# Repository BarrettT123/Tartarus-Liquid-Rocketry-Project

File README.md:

Files and photos related to my work on the Tartarus Project of the Space Hardware Club

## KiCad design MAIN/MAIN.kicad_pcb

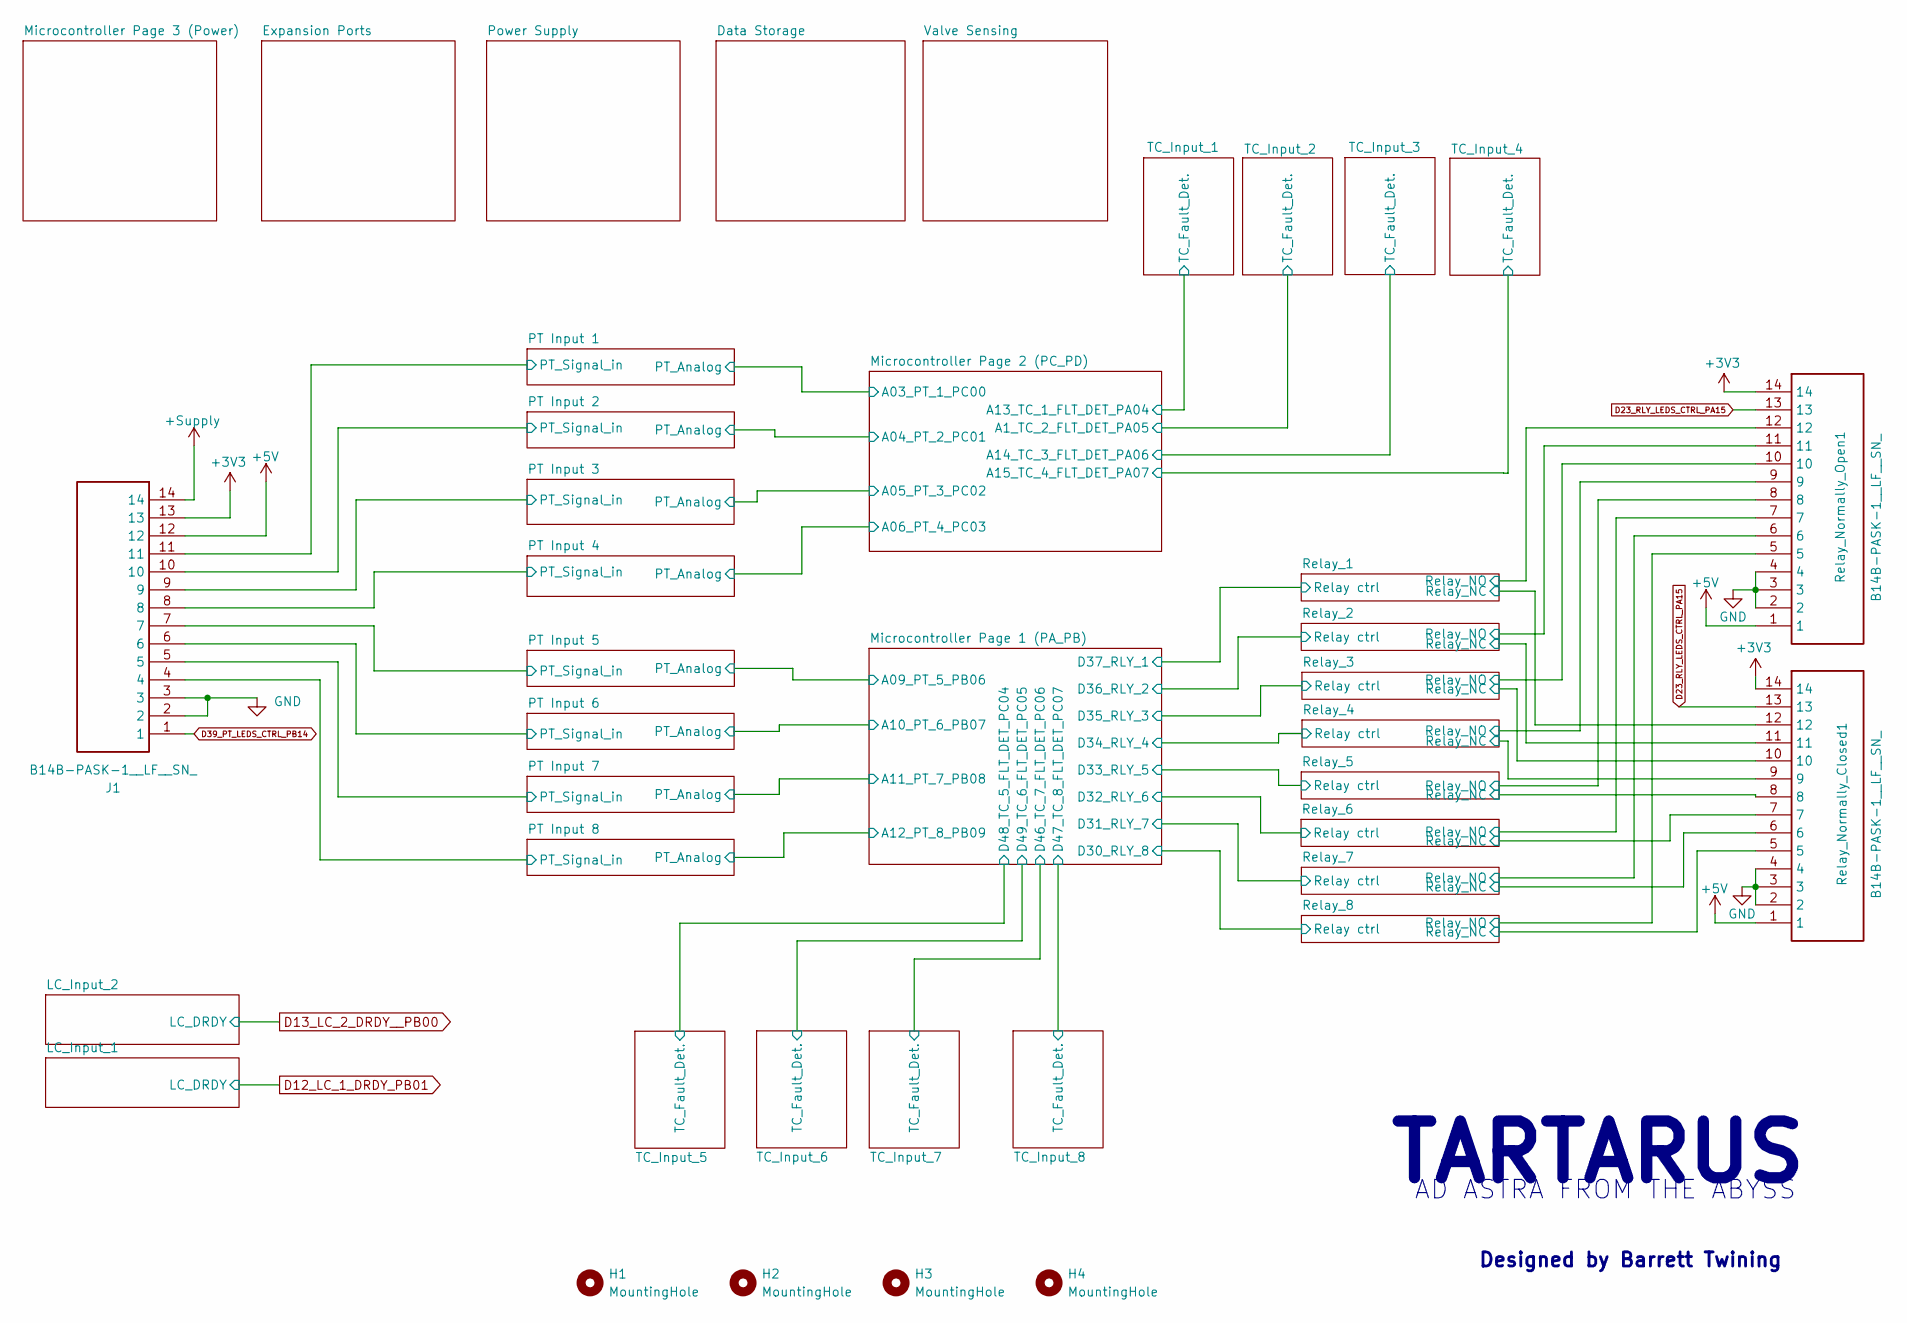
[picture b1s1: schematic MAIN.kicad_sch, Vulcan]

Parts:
H1, H2, H3, H4: MountingHole; MountingHole_3.2mm_M3_ISO7380_Pad_TopBottom
J1: B14B-PASK-1__LF__SN_; B14BPASK1LFSN; Manufacturer_Part_Number B14B-PASK-1 (LF)(SN)
Relay_Normally_Closed1: B14B-PASK-1__LF__SN_; B14BPASK1LFSN; Manufacturer_Part_Number B14B-PASK-1 (LF)(SN)
Relay_Normally_Open1: B14B-PASK-1__LF__SN_; B14BPASK1LFSN; Manufacturer_Part_Number B14B-PASK-1 (LF)(SN)

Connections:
+3V3: J1.13, Relay_Normally_Closed1.14, Relay_Normally_Open1.14; also elsewhere on the board
+5V: J1.12, Relay_Normally_Closed1.1, Relay_Normally_Open1.1; also elsewhere on the board
+Supply: J1.14; also elsewhere on the board
/PT Input 1/PT_Signal_in: J1.11; also elsewhere on the board
/PT Input 2/PT_Signal_in: J1.10; also elsewhere on the board
/PT Input 3/PT_Signal_in: J1.9; also elsewhere on the board
/PT Input 4/PT_Signal_in: J1.8; also elsewhere on the board
/PT Input 5/PT_Signal_in: J1.7; also elsewhere on the board
/PT Input 6/PT_Signal_in: J1.6; also elsewhere on the board
/PT Input 7/PT_Signal_in: J1.5; also elsewhere on the board
/PT Input 8/PT_Signal_in: J1.4; also elsewhere on the board
/Relay_1/Relay_NC: Relay_Normally_Closed1.12; also elsewhere on the board
/Relay_1/Relay_NO: Relay_Normally_Open1.12; also elsewhere on the board
/Relay_2/Relay_NC: Relay_Normally_Closed1.11; also elsewhere on the board
/Relay_2/Relay_NO: Relay_Normally_Open1.11; also elsewhere on the board
/Relay_3/Relay_NC: Relay_Normally_Closed1.10; also elsewhere on the board
/Relay_3/Relay_NO: Relay_Normally_Open1.10; also elsewhere on the board
/Relay_4/Relay_NC: Relay_Normally_Closed1.9; also elsewhere on the board
/Relay_4/Relay_NO: Relay_Normally_Open1.9; also elsewhere on the board
/Relay_5/Relay_NC: Relay_Normally_Closed1.8; also elsewhere on the board
/Relay_5/Relay_NO: Relay_Normally_Open1.8; also elsewhere on the board
/Relay_6/Relay_NC: Relay_Normally_Closed1.7; also elsewhere on the board
/Relay_6/Relay_NO: Relay_Normally_Open1.7; also elsewhere on the board
/Relay_7/Relay_NC: Relay_Normally_Closed1.6; also elsewhere on the board
/Relay_7/Relay_NO: Relay_Normally_Open1.6; also elsewhere on the board
/Relay_8/Relay_NC: Relay_Normally_Closed1.5; also elsewhere on the board
/Relay_8/Relay_NO: Relay_Normally_Open1.5; also elsewhere on the board
D23_RLY_LEDS_CTRL_PA15: Relay_Normally_Closed1.13, Relay_Normally_Open1.13; also elsewhere on the board
D39_PT_LEDS_CTRL_PB14: J1.1; also elsewhere on the board
GND: J1.2, J1.3, Relay_Normally_Closed1.2, Relay_Normally_Closed1.3, Relay_Normally_Closed1.4, Relay_Normally_Open1.2, Relay_Normally_Open1.3, Relay_Normally_Open1.4; also elsewhere on the board

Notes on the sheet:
Designed by Barrett Twining
TARTARUS
AD ASTRA FROM THE ABYSS

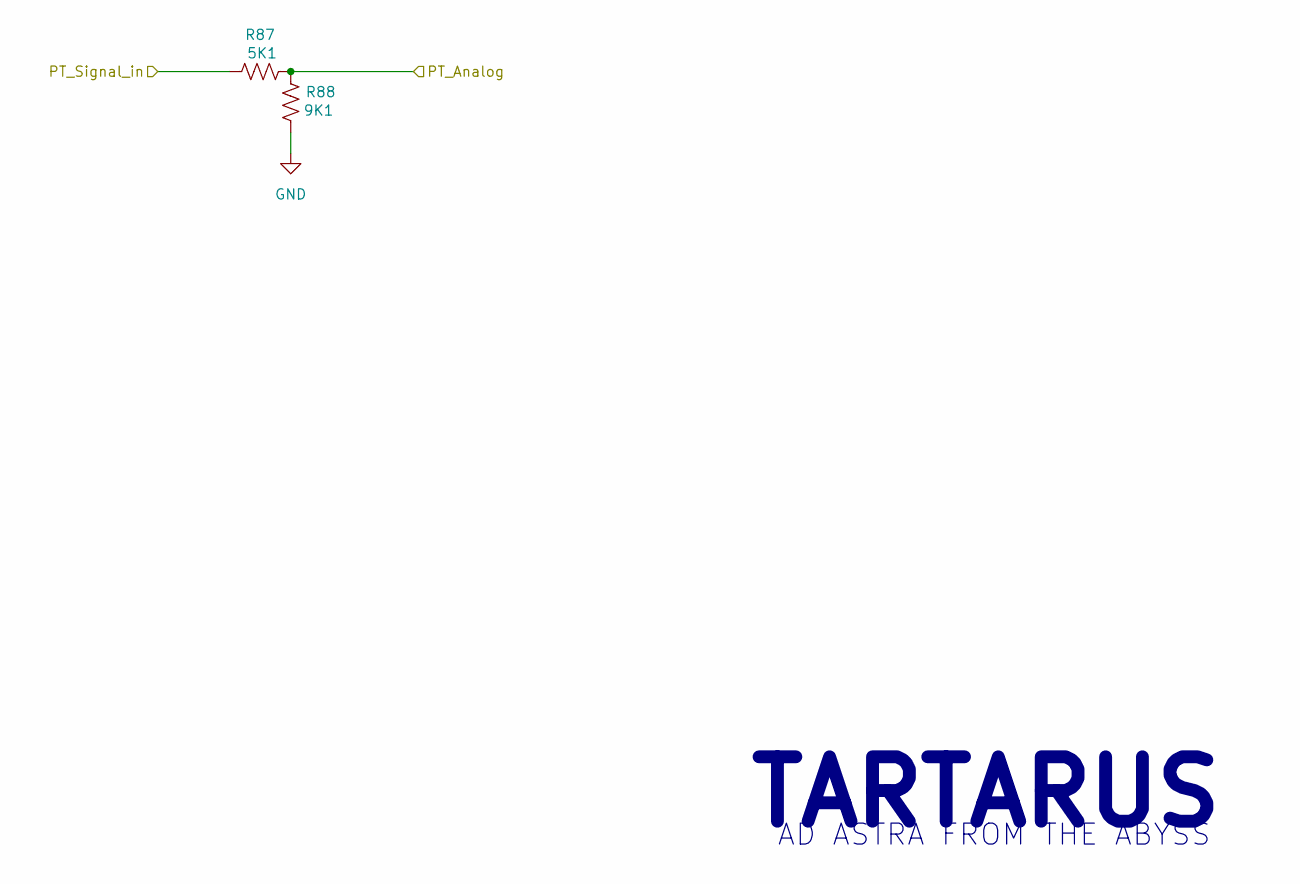
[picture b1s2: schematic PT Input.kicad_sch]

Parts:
R87: 5K1; R_0603_1608Metric
R88: 9K1; R_0603_1608Metric

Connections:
/PT Input 1/PT_Signal_in: R87.1; also elsewhere on the board
A03_PT_1_PC00: R87.2, R88.1; also elsewhere on the board
GND: R88.2; also elsewhere on the board

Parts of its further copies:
R89, R91, R93, R95, R97, R99, R101: 5K1; R_0603_1608Metric
R90, R92, R94, R96, R98, R100, R102: 9K1; R_0603_1608Metric

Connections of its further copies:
/Microcontroller Page 1 (PA_PB)/A09_PT_5_PB06: R95.2, R96.1; also elsewhere on the board
/Microcontroller Page 1 (PA_PB)/A10_PT_6_PB07: R97.2, R98.1; also elsewhere on the board
/Microcontroller Page 1 (PA_PB)/A11_PT_7_PB08: R99.2, R100.1; also elsewhere on the board
/Microcontroller Page 1 (PA_PB)/A12_PT_8_PB09: R101.2, R102.1; also elsewhere on the board
/PT Input 2/PT_Signal_in: R89.1; also elsewhere on the board
/PT Input 3/PT_Signal_in: R91.1; also elsewhere on the board
/PT Input 4/PT_Signal_in: R93.1; also elsewhere on the board
/PT Input 5/PT_Signal_in: R95.1; also elsewhere on the board
/PT Input 6/PT_Signal_in: R97.1; also elsewhere on the board
/PT Input 7/PT_Signal_in: R99.1; also elsewhere on the board
/PT Input 8/PT_Signal_in: R101.1; also elsewhere on the board
A04_PT_2_PC01: R89.2, R90.1; also elsewhere on the board
A05_PT_3_PC02: R91.2, R92.1; also elsewhere on the board
A06_PT_4_PC03: R93.2, R94.1; also elsewhere on the board
GND: R90.2, R92.2, R94.2, R96.2, R98.2, R100.2, R102.2; also elsewhere on the board

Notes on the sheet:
AD ASTRA FROM THE ABYSS
TARTARUS

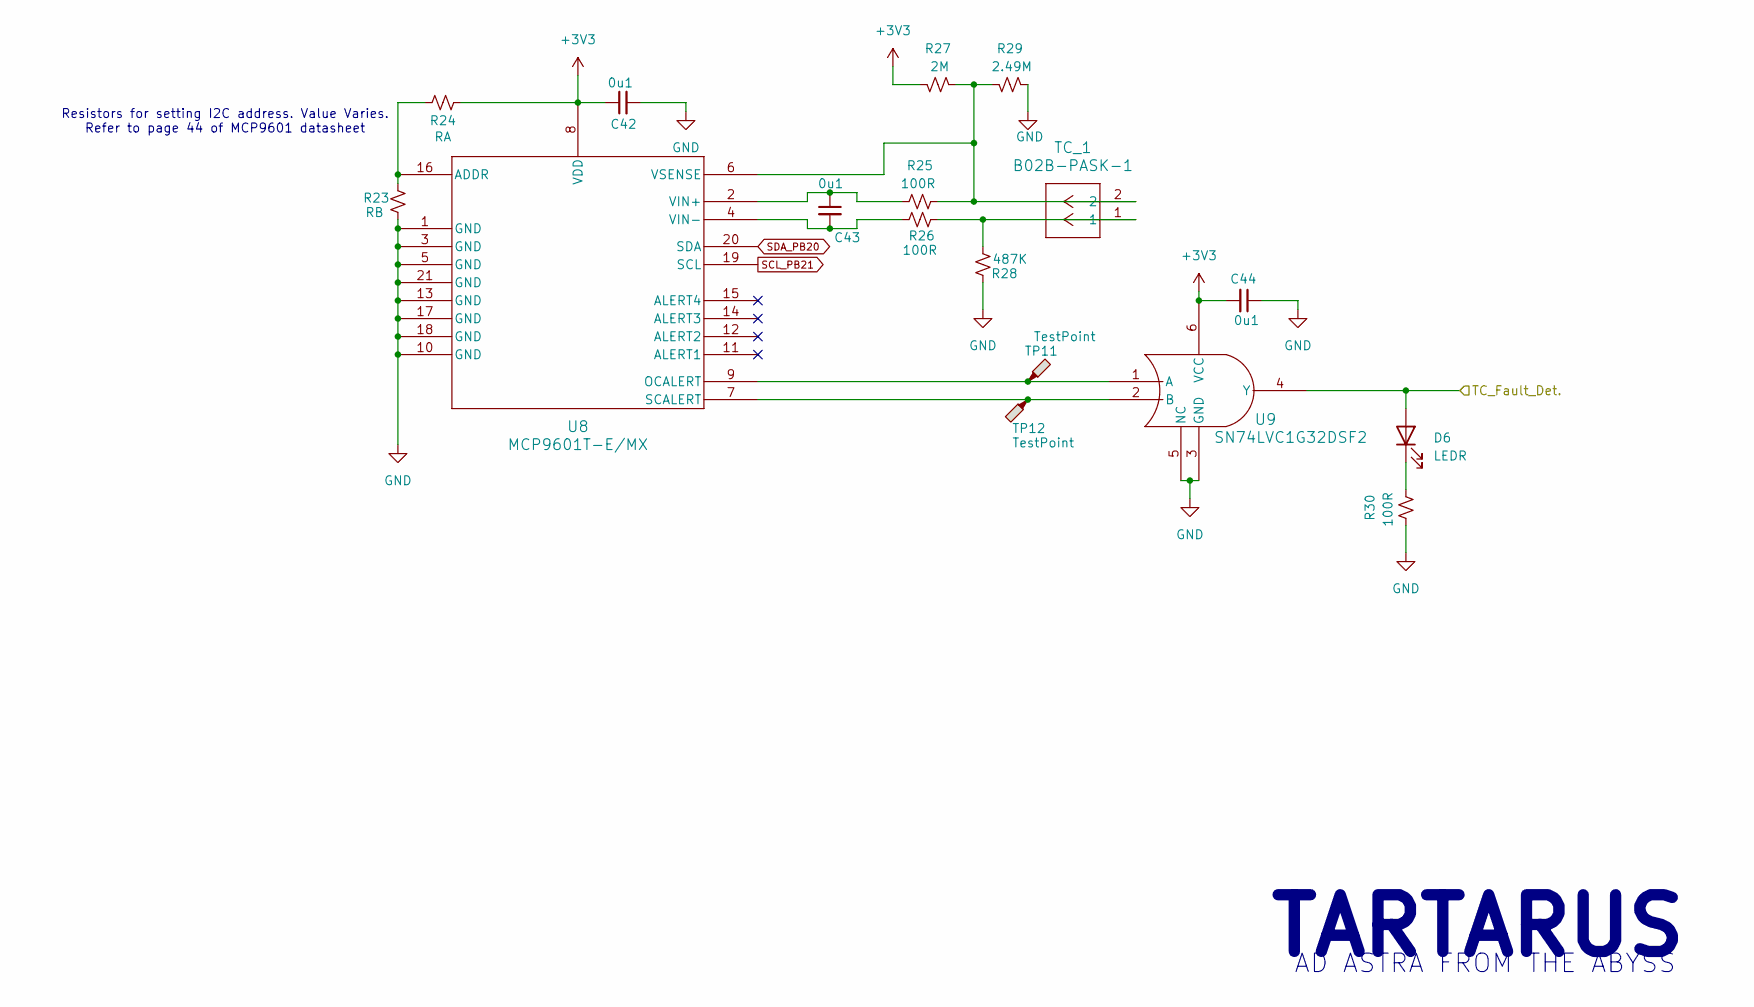
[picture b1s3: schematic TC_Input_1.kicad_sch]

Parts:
C42, C43, C44: 0u1; C_0603_1608Metric
D6: LEDR; LED_0603_1608Metric
R23: RB; R_0603_1608Metric
R24: RA; R_0603_1608Metric
R25, R26, R30: 100R; R_0603_1608Metric
R27: 2M; R_0603_1608Metric
R28: 487K; R_0603_1608Metric
R29: 2.49M; R_0603_1608Metric
TC_1: B02B-PASK-1; CONN_B02B-PASK-1_JST
TP11, TP12: TestPoint; TestPoint_Pad_D1.0mm
U8: MCP9601T-E/MX; MCP9601T_E_MX
U9: SN74LVC1G32DSF2; DSF6

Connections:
+3V3: C42.1, C44.2, R24.2, R27.2, U8.8 (VDD), U9.6 (VCC); also elsewhere on the board
/Microcontroller Page 2 (PC_PD)/A13_TC_1_FLT_DET_PA04: D6.2 (A), U9.4 (Y); also elsewhere on the board
GND: C42.2, C44.1, R23.1, R28.1, R29.1, R30.1, U8.1 (GND), U8.3 (GND), U8.5 (GND), U8.10 (GND), U8.13 (GND), U8.17 (GND), U8.18 (GND), U8.21 (GND), U9.3 (GND), U9.5 (NC); also elsewhere on the board
unnamed: D6.1 (K), R30.2
unnamed: R26.2, R28.2, TC_1.1
unnamed: R23.2, R24.1, U8.16 (ADDR)
unnamed: TP11.1, U8.9 (OCALERT), U9.1 (A)
unnamed: TP12.1, U8.7 (SCALERT), U9.2 (B)
unnamed: C43.1, R25.1, U8.2 (VIN+)
unnamed: C43.2, R26.1, U8.4 (VIN-)
unnamed: R25.2, R27.1, R29.2, TC_1.2, U8.6 (VSENSE)
SCL_PB21: U8.19 (SCL); also elsewhere on the board
SDA_PB20: U8.20 (SDA); also elsewhere on the board

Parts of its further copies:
C45, C46, C47, C48, C49, C50, C51, C52, C53, C54, C55, C56, C57, C58, C59, C60, C61, C62, C63, C64, C65: 0u1; C_0603_1608Metric
D7, D8, D9, D10, D11, D12, D13: LEDR; LED_0603_1608Metric
R31, R39, R47, R55, R63, R71, R79: RB; R_0603_1608Metric
R32, R40, R48, R56, R64, R72, R80: RA; R_0603_1608Metric
R33, R34, R38, R41, R42, R46, R49, R50, R54, R57, R58, R62, R65, R66, R70, R73, R74, R78, R81, R82, R86: 100R; R_0603_1608Metric
R35, R43, R51, R59, R67, R75, R83: 2M; R_0603_1608Metric
R36, R44, R52, R60, R68, R76, R84: 487K; R_0603_1608Metric
R37, R45, R53, R61, R69, R77, R85: 2.49M; R_0603_1608Metric
TC_2, TC_3, TC_4, TC_5, TC_6, TC_7, TC_8: B02B-PASK-1; CONN_B02B-PASK-1_JST
TP13, TP14, TP15, TP16, TP17, TP18, TP19, TP20, TP21, TP22, TP23, TP24, TP25, TP26: TestPoint; TestPoint_Pad_D1.0mm
U10, U12, U14, U16, U18, U20, U22: MCP9601T-E/MX; MCP9601T_E_MX
U11, U13, U15, U17, U19, U21, U23: SN74LVC1G32DSF2; DSF6

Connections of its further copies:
+3V3: C45.1, C47.2, C48.1, C50.2, C51.1, C53.2, C54.1, C56.2, C57.1, C59.2, C60.1, C62.2, C63.1, C65.2, R32.2, R35.2, R40.2, R43.2, R48.2, R51.2, R56.2, R59.2, R64.2, R67.2, R72.2, R75.2, R80.2, R83.2, U10.8 (VDD), U11.6 (VCC), U12.8 (VDD), U13.6 (VCC), U14.8 (VDD), U15.6 (VCC), U16.8 (VDD), U17.6 (VCC), U18.8 (VDD), U19.6 (VCC), U20.8 (VDD), U21.6 (VCC), U22.8 (VDD), U23.6 (VCC); also elsewhere on the board
/Microcontroller Page 1 (PA_PB)/D46_TC_7_FLT_DET_PC06: D12.2 (A), U21.4 (Y); also elsewhere on the board
/Microcontroller Page 1 (PA_PB)/D47_TC_8_FLT_DET_PC07: D13.2 (A), U23.4 (Y); also elsewhere on the board
/Microcontroller Page 1 (PA_PB)/D48_TC_5_FLT_DET_PC04: D10.2 (A), U17.4 (Y); also elsewhere on the board
/Microcontroller Page 1 (PA_PB)/D49_TC_6_FLT_DET_PC05: D11.2 (A), U19.4 (Y); also elsewhere on the board
/Microcontroller Page 2 (PC_PD)/A1_TC_2_FLT_DET_PA05: D7.2 (A), U11.4 (Y); also elsewhere on the board
/Microcontroller Page 2 (PC_PD)/A14_TC_3_FLT_DET_PA06: D8.2 (A), U13.4 (Y); also elsewhere on the board
/Microcontroller Page 2 (PC_PD)/A15_TC_4_FLT_DET_PA07: D9.2 (A), U15.4 (Y); also elsewhere on the board
GND: C45.2, C47.1, C48.2, C50.1, C51.2, C53.1, C54.2, C56.1, C57.2, C59.1, C60.2, C62.1, C63.2, C65.1, R31.1, R36.1, R37.1, R38.1, R39.1, R44.1, R45.1, R46.1, R47.1, R52.1, R53.1, R54.1, R55.1, R60.1, R61.1, R62.1, R63.1, R68.1, R69.1, R70.1, R71.1, R76.1, R77.1, R78.1, R79.1, R84.1, R85.1, R86.1, U10.1 (GND), U10.3 (GND), U10.5 (GND), U10.10 (GND), U10.13 (GND), U10.17 (GND), U10.18 (GND), U10.21 (GND), U11.3 (GND), U11.5 (NC), U12.1 (GND), U12.3 (GND), U12.5 (GND), U12.10 (GND), U12.13 (GND), U12.17 (GND), U12.18 (GND), U12.21 (GND), U13.3 (GND), U13.5 (NC), U14.1 (GND), U14.3 (GND), U14.5 (GND), U14.10 (GND), U14.13 (GND), U14.17 (GND), U14.18 (GND), U14.21 (GND), U15.3 (GND), U15.5 (NC), U16.1 (GND), U16.3 (GND), U16.5 (GND), U16.10 (GND), U16.13 (GND), U16.17 (GND), U16.18 (GND), U16.21 (GND), U17.3 (GND), U17.5 (NC), U18.1 (GND), U18.3 (GND), U18.5 (GND), U18.10 (GND), U18.13 (GND), U18.17 (GND), U18.18 (GND), U18.21 (GND), U19.3 (GND), U19.5 (NC), U20.1 (GND), U20.3 (GND), U20.5 (GND), U20.10 (GND), U20.13 (GND), U20.17 (GND), U20.18 (GND), U20.21 (GND), U21.3 (GND), U21.5 (NC), U22.1 (GND), U22.3 (GND), U22.5 (GND), U22.10 (GND), U22.13 (GND), U22.17 (GND), U22.18 (GND), U22.21 (GND), U23.3 (GND), U23.5 (NC); also elsewhere on the board
unnamed: D7.1 (K), R38.2
unnamed: D8.1 (K), R46.2
unnamed: D9.1 (K), R54.2
unnamed: D10.1 (K), R62.2
unnamed: D11.1 (K), R70.2
unnamed: D12.1 (K), R78.2
unnamed: D13.1 (K), R86.2
unnamed: R34.2, R36.2, TC_2.1
unnamed: R42.2, R44.2, TC_3.1
unnamed: R50.2, R52.2, TC_4.1
unnamed: R58.2, R60.2, TC_5.1
unnamed: R66.2, R68.2, TC_6.1
unnamed: R74.2, R76.2, TC_7.1
unnamed: R82.2, R84.2, TC_8.1
unnamed: R31.2, R32.1, U10.16 (ADDR)
unnamed: TP13.1, U10.9 (OCALERT), U11.1 (A)
unnamed: TP14.1, U10.7 (SCALERT), U11.2 (B)
unnamed: C46.1, R33.1, U10.2 (VIN+)
unnamed: C46.2, R34.1, U10.4 (VIN-)
unnamed: R33.2, R35.1, R37.2, TC_2.2, U10.6 (VSENSE)
unnamed: R39.2, R40.1, U12.16 (ADDR)
unnamed: TP15.1, U12.9 (OCALERT), U13.1 (A)
unnamed: TP16.1, U12.7 (SCALERT), U13.2 (B)
unnamed: C49.1, R41.1, U12.2 (VIN+)
unnamed: C49.2, R42.1, U12.4 (VIN-)
unnamed: R41.2, R43.1, R45.2, TC_3.2, U12.6 (VSENSE)
unnamed: R47.2, R48.1, U14.16 (ADDR)
unnamed: TP17.1, U14.9 (OCALERT), U15.1 (A)
unnamed: TP18.1, U14.7 (SCALERT), U15.2 (B)
unnamed: C52.1, R49.1, U14.2 (VIN+)
unnamed: C52.2, R50.1, U14.4 (VIN-)
unnamed: R49.2, R51.1, R53.2, TC_4.2, U14.6 (VSENSE)
unnamed: R55.2, R56.1, U16.16 (ADDR)
unnamed: TP19.1, U16.9 (OCALERT), U17.1 (A)
unnamed: TP20.1, U16.7 (SCALERT), U17.2 (B)
unnamed: C55.1, R57.1, U16.2 (VIN+)
unnamed: C55.2, R58.1, U16.4 (VIN-)
unnamed: R57.2, R59.1, R61.2, TC_5.2, U16.6 (VSENSE)
unnamed: R63.2, R64.1, U18.16 (ADDR)
unnamed: TP21.1, U18.9 (OCALERT), U19.1 (A)
unnamed: TP22.1, U18.7 (SCALERT), U19.2 (B)
unnamed: C58.1, R65.1, U18.2 (VIN+)
unnamed: C58.2, R66.1, U18.4 (VIN-)
unnamed: R65.2, R67.1, R69.2, TC_6.2, U18.6 (VSENSE)
unnamed: R71.2, R72.1, U20.16 (ADDR)
unnamed: TP23.1, U20.9 (OCALERT), U21.1 (A)
unnamed: TP24.1, U20.7 (SCALERT), U21.2 (B)
unnamed: C61.1, R73.1, U20.2 (VIN+)
unnamed: C61.2, R74.1, U20.4 (VIN-)
unnamed: R73.2, R75.1, R77.2, TC_7.2, U20.6 (VSENSE)
unnamed: R79.2, R80.1, U22.16 (ADDR)
unnamed: TP25.1, U22.9 (OCALERT), U23.1 (A)
unnamed: TP26.1, U22.7 (SCALERT), U23.2 (B)
unnamed: C64.1, R81.1, U22.2 (VIN+)
unnamed: C64.2, R82.1, U22.4 (VIN-)
unnamed: R81.2, R83.1, R85.2, TC_8.2, U22.6 (VSENSE)
SCL_PB21: U10.19 (SCL), U12.19 (SCL), U14.19 (SCL), U16.19 (SCL), U18.19 (SCL), U20.19 (SCL), U22.19 (SCL); also elsewhere on the board
SDA_PB20: U10.20 (SDA), U12.20 (SDA), U14.20 (SDA), U16.20 (SDA), U18.20 (SDA), U20.20 (SDA), U22.20 (SDA); also elsewhere on the board

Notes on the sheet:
TARTARUS
AD ASTRA FROM THE ABYSS
Resistors for setting I2C address. Value Varies. Refer to page 44 of MCP9601 datasheet

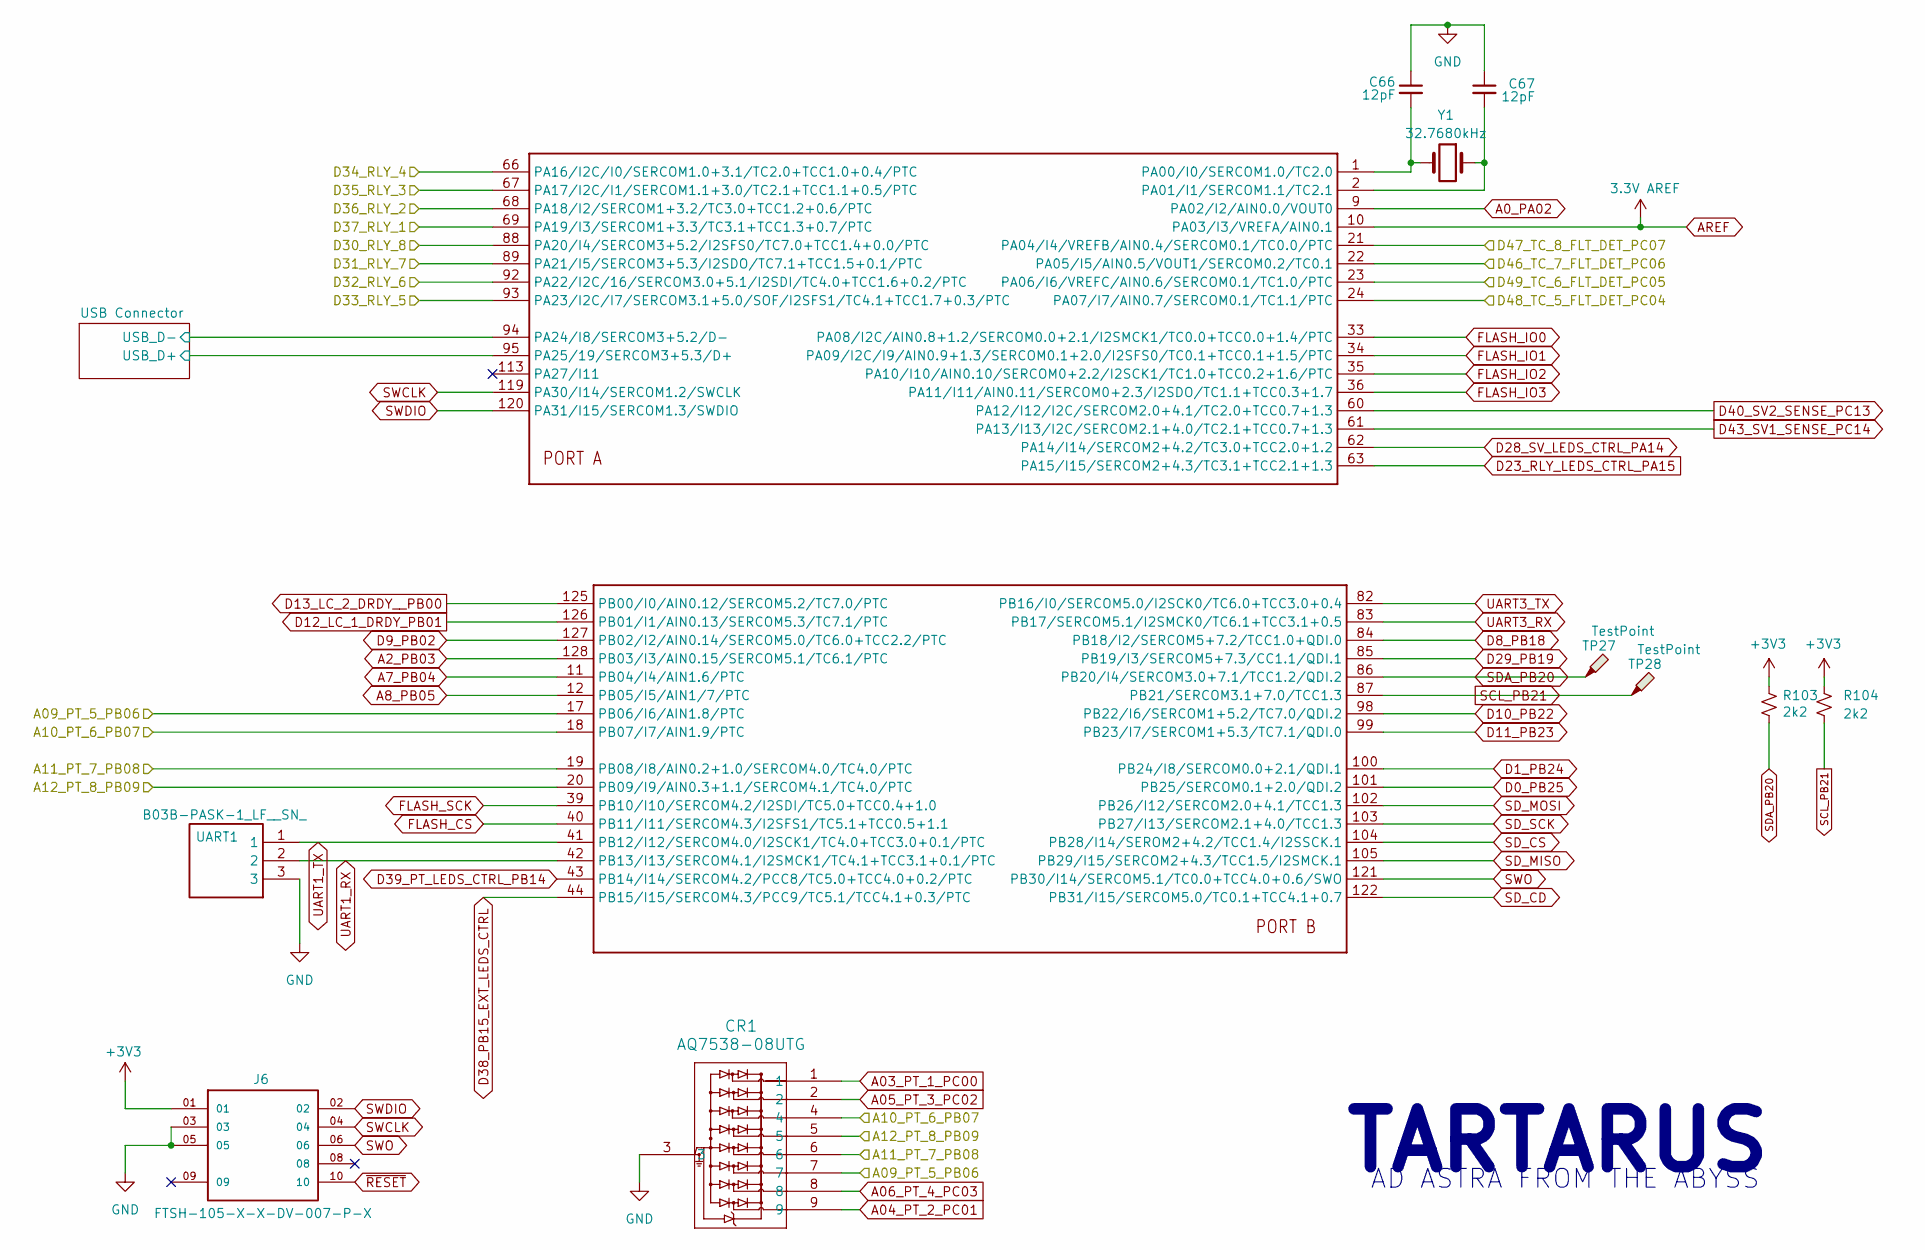
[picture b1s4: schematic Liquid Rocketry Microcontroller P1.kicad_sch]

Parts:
C66, C67: 12pF; C_0603_1608Metric
CR1: AQ7538-08UTG; uDFN-9_3p8x1p0_LTF
J6: FTSH-105-X-X-DV-007-P-X; SAMTEC_FTSH-105-01-X-D-007-K; PARTREV H
R103, R104: 2k2; R_0603_1608Metric
TP27, TP28: TestPoint; TestPoint_Pad_D1.0mm
U$1: SAMD51PXXA; SAMD51P20A-AF
UART1: B03B-PASK-1_LF__SN_; B03BPASK1LFSN; Mouser Part Number 306-B03BPASK1LFSN
Y1: 32.7680kHz; WE-XTAL_IQXC-90

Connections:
+3V3: J6.01, R103.1, R104.1; also elsewhere on the board
/Microcontroller Page 1 (PA_PB)/A09_PT_5_PB06: CR1.7, U$1.17 (PB06/I6/AIN1.8/PTC); also elsewhere on the board
/Microcontroller Page 1 (PA_PB)/A10_PT_6_PB07: CR1.4, U$1.18 (PB07/I7/AIN1.9/PTC); also elsewhere on the board
/Microcontroller Page 1 (PA_PB)/A11_PT_7_PB08: CR1.6, U$1.19 (PB08/I8/AIN0.2+1.0/SERCOM4.0/TC4.0/PTC); also elsewhere on the board
/Microcontroller Page 1 (PA_PB)/A12_PT_8_PB09: CR1.5, U$1.20 (PB09/I9/AIN0.3+1.1/SERCOM4.1/TC4.0/PTC); also elsewhere on the board
/Microcontroller Page 1 (PA_PB)/D30_RLY_8: U$1.88 (PA20/I4/SERCOM3+5.2/I2SFS0/TC7.0+TCC1.4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); also elsewhere on the board
/Microcontroller Page 1 (PA_PB)/D31_RLY_7: U$1.89 (PA21/I5/SERCOM3+5.3/I2SDO/TC7.1+TCC1.5+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); also elsewhere on the board
/Microcontroller Page 1 (PA_PB)/D32_RLY_6: U$1.92 (PA22/I2C/16/SERCOM3.0+5.1/I2SDI/TC4.0+T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); also elsewhere on the board
/Microcontroller Page 1 (PA_PB)/D33_RLY_5: U$1.93 (PA23/I2C/I7/SERCOM3.1+5.0/SOF/I2SFS1/TC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); also elsewhere on the board
/Microcontroller Page 1 (PA_PB)/D34_RLY_4: U$1.66 (PA16/I2C/I0/SERCOM1.0+3.1/TC2.0+TCC1.0+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); also elsewhere on the board
/Microcontroller Page 1 (PA_PB)/D35_RLY_3: U$1.67 (PA17/I2C/I1/SERCOM1.1+3.0/TC2.1+TCC1.1+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); also elsewhere on the board
/Microcontroller Page 1 (PA_PB)/D36_RLY_2: U$1.68 (PA18/I2/SERCOM1+3.2/TC3.0+TCC1.2+0.6/PTC); also elsewhere on the board
/Microcontroller Page 1 (PA_PB)/D37_RLY_1: U$1.69 (PA19/I3/SERCOM1+3.3/TC3.1+TCC1.3+0.7/PTC); also elsewhere on the board
/Microcontroller Page 1 (PA_PB)/D46_TC_7_FLT_DET_PC06: U$1.22 (PA05/I5/AIN0.5/VOUT1/SERCOM0.2/TC0.1); also elsewhere on the board
/Microcontroller Page 1 (PA_PB)/D47_TC_8_FLT_DET_PC07: U$1.21 (PA04/I4/VREFB/AIN0.4/SERCOM0.1/TC0.0/PTC); also elsewhere on the board
/Microcontroller Page 1 (PA_PB)/D48_TC_5_FLT_DET_PC04: U$1.24 (PA07/I7/AIN0.7/SERCOM0.1/TC1.1/PTC); also elsewhere on the board
/Microcontroller Page 1 (PA_PB)/D49_TC_6_FLT_DET_PC05: U$1.23 (PA06/I6/VREFC/AIN0.6/SERCOM0.1/TC1.0/PTC); also elsewhere on the board
/Microcontroller Page 1 (PA_PB)/USB Connector/USB_D+: U$1.95 (PA25/19/SERCOM3+5.3/D+); also elsewhere on the board
/Microcontroller Page 1 (PA_PB)/USB Connector/USB_D-: U$1.94 (PA24/I8/SERCOM3+5.2/D-); also elsewhere on the board
A0_PA02: U$1.9 (PA02/I2/AIN0.0/VOUT0); also elsewhere on the board
A2_PB03: U$1.128 (PB03/I3/AIN0.15/SERCOM5.1/TC6.1/PTC); also elsewhere on the board
A03_PT_1_PC00: CR1.1; also elsewhere on the board
A04_PT_2_PC01: CR1.9; also elsewhere on the board
A05_PT_3_PC02: CR1.2; also elsewhere on the board
A06_PT_4_PC03: CR1.8; also elsewhere on the board
A7_PB04: U$1.11 (PB04/I4/AIN1.6/PTC); also elsewhere on the board
A8_PB05: U$1.12 (PB05/I5/AIN1/7/PTC); also elsewhere on the board
AREF: U$1.10 (PA03/I3/VREFA/AIN0.1); also elsewhere on the board
D0_PB25: U$1.101 (PB25/SERCOM0.1+2.0/QDI.2); also elsewhere on the board
D1_PB24: U$1.100 (PB24/I8/SERCOM0.0+2.1/QDI.1); also elsewhere on the board
D8_PB18: U$1.84 (PB18/I2/SERCOM5+7.2/TCC1.0+QDI.0); also elsewhere on the board
D9_PB02: U$1.127 (PB02/I2/AIN0.14/SERCOM5.0/TC6.0+TCC2.2/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); also elsewhere on the board
D10_PB22: U$1.98 (PB22/I6/SERCOM1+5.2/TC7.0/QDI.2); also elsewhere on the board
D11_PB23: U$1.99 (PB23/I7/SERCOM1+5.3/TC7.1/QDI.0); also elsewhere on the board
D12_LC_1_DRDY_PB01: U$1.126 (PB01/I1/AIN0.13/SERCOM5.3/TC7.1/PTC); also elsewhere on the board
D13_LC_2_DRDY__PB00: U$1.125 (PB00/I0/AIN0.12/SERCOM5.2/TC7.0/PTC); also elsewhere on the board
D23_RLY_LEDS_CTRL_PA15: U$1.63 (PA15/I15/SERCOM2+4.3/TC3.1+TCC2.1+1.3); also elsewhere on the board
D28_SV_LEDS_CTRL_PA14: U$1.62 (PA14/I14/SERCOM2+4.2/TC3.0+TCC2.0+1.2); also elsewhere on the board
D29_PB19: U$1.85 (PB19/I3/SERCOM5+7.3/CC1.1/QDI.1); also elsewhere on the board
D38_PB15_EXT_LEDS_CTRL: U$1.44 (PB15/I15/SERCOM4.3/PCC9/TC5.1/TCC4.1+0.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); also elsewhere on the board
D39_PT_LEDS_CTRL_PB14: U$1.43 (PB14/I14/SERCOM4.2/PCC8/TC5.0+TCC4.0+0.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); also elsewhere on the board
D40_SV2_SENSE_PC13: U$1.60 (PA12/I12/I2C/SERCOM2.0+4.1/TC2.0+TCC0.7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); also elsewhere on the board
D43_SV1_SENSE_PC14: U$1.61 (PA13/I13/I2C/SERCOM2.1+4.0/TC2.1+TCC0.7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); also elsewhere on the board
FLASH_CS: U$1.40 (PB11/I11/SERCOM4.3/I2SFS1/TC5.1+TCC0.5+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); also elsewhere on the board
FLASH_IO0: U$1.33 (PA08/I2C/AIN0.8+1.2/SERCOM0.0+2.1/I2SMC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); also elsewhere on the board
FLASH_IO1: U$1.34 (PA09/I2C/I9/AIN0.9+1.3/SERCOM0.1+2.0/I2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); also elsewhere on the board
FLASH_IO2: U$1.35 (PA10/I10/AIN0.10/SERCOM0+2.2/I2SCK1/TC1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); also elsewhere on the board
FLASH_IO3: U$1.36 (PA11/I11/AIN0.11/SERCOM0+2.3/I2SDO/TC1.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); also elsewhere on the board
FLASH_SCK: U$1.39 (PB10/I10/SERCOM4.2/I2SDI/TC5.0+TCC0.4+1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); also elsewhere on the board
GND: C66.1, C67.1, CR1.3, J6.03, J6.05, UART1.3; also elsewhere on the board
unnamed: C66.2, U$1.1 (PA00/I0/SERCOM1.0/TC2.0), Y1.2
unnamed: C67.2, U$1.2 (PA01/I1/SERCOM1.1/TC2.1), Y1.1
SCL_PB21: R104.2, TP28.1, U$1.87 (PB21/SERCOM3.1+7.0/TCC1.3); also elsewhere on the board
SDA_PB20: R103.2, TP27.1, U$1.86 (PB20/I4/SERCOM3.0+7.1/TCC1.2/QDI.2); also elsewhere on the board
SD_CD: U$1.122 (PB31/I15/SERCOM5.0/TC0.1+TCC4.1+0.7); also elsewhere on the board
SD_CS: U$1.104 (PB28/I14/SEROM2+4.2/TCC1.4/I2SSCK.1); also elsewhere on the board
SD_MISO: U$1.105 (PB29/I15/SERCOM2+4.3/TCC1.5/I2SMCK.1); also elsewhere on the board
SD_MOSI: U$1.102 (PB26/I12/SERCOM2.0+4.1/TCC1.3); also elsewhere on the board
SD_SCK: U$1.103 (PB27/I13/SERCOM2.1+4.0/TCC1.3); also elsewhere on the board
SWCLK: J6.04, U$1.119 (PA30/I14/SERCOM1.2/SWCLK)
SWDIO: J6.02, U$1.120 (PA31/I15/SERCOM1.3/SWDIO)
SWO: J6.06, U$1.121 (PB30/I14/SERCOM5.1/TC0.0+TCC4.0+0.6/SWO)
UART1_RX: U$1.42 (PB13/I13/SERCOM4.1/I2SMCK1/TC4.1+TCC3.1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), UART1.2
UART1_TX: U$1.41 (PB12/I12/SERCOM4.0/I2SCK1/TC4.0+TCC3.0+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), UART1.1
UART3_RX: U$1.83 (PB17/SERCOM5.1/I2SMCK0/TC6.1+TCC3.1+0.5); also elsewhere on the board
UART3_TX: U$1.82 (PB16/I0/SERCOM5.0/I2SCK0/TC6.0+TCC3.0+0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); also elsewhere on the board
~RESET: J6.10; also elsewhere on the board

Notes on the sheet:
TARTARUS
AD ASTRA FROM THE ABYSS

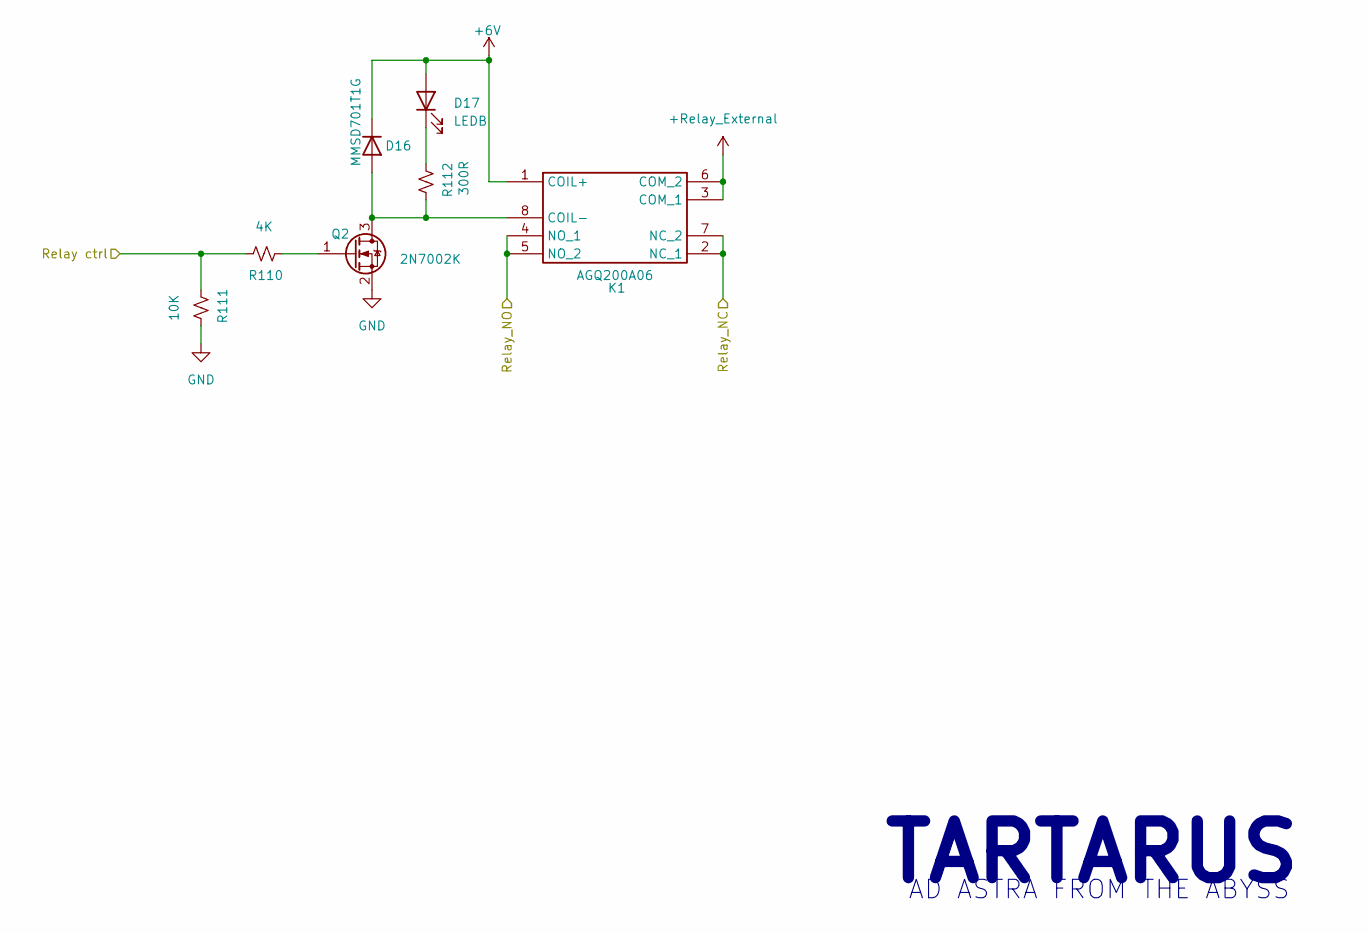
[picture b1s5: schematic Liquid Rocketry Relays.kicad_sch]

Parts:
D16: MMSD701T1G
D17: LEDB; LED_0603_1608Metric
K1: AGQ200A06; RELAY_AGQ_A_PAN_AGQ200A06; Mouser Part Number 769-AGQ200A12Z
Q2: 2N7002K; 2N7002K_ONS
R110: 4K; R_0603_1608Metric
R111: 10K; R_0603_1608Metric
R112: 300R; R_0603_1608Metric

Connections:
+6V: D16.1 (K), D17.2 (A), K1.1 (COIL+); also elsewhere on the board
+Relay_External: K1.3 (COM_1), K1.6 (COM_2); also elsewhere on the board
/Microcontroller Page 1 (PA_PB)/D37_RLY_1: R110.2, R111.1; also elsewhere on the board
/Relay_1/Relay_NC: K1.2 (NC_1), K1.7 (NC_2); also elsewhere on the board
/Relay_1/Relay_NO: K1.4 (NO_1), K1.5 (NO_2); also elsewhere on the board
GND: Q2.2 (S), R111.2; also elsewhere on the board
unnamed: D16.2 (A), K1.8 (COIL-), Q2.3 (D), R112.2
unnamed: D17.1 (K), R112.1
unnamed: Q2.1 (G), R110.1

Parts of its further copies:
D18, D20, D22, D24, D26, D28, D30: MMSD701T1G
D19, D21, D23, D25, D27, D29, D31: LEDB; LED_0603_1608Metric
K2, K3, K4, K5, K6, K7, K8: AGQ200A06; RELAY_AGQ_A_PAN_AGQ200A06; Mouser Part Number 769-AGQ200A12Z
Q3, Q4, Q5, Q6, Q7, Q8, Q9: 2N7002K; 2N7002K_ONS
R113, R116, R119, R122, R125, R128, R131: 4K; R_0603_1608Metric
R114, R117, R120, R123, R126, R129, R132: 10K; R_0603_1608Metric
R115, R118, R121, R124, R127, R130, R133: 300R; R_0603_1608Metric

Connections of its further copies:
+6V: D18.1 (K), D19.2 (A), D20.1 (K), D21.2 (A), D22.1 (K), D23.2 (A), D24.1 (K), D25.2 (A), D26.1 (K), D27.2 (A), D28.1 (K), D29.2 (A), D30.1 (K), D31.2 (A), K2.1 (COIL+), K3.1 (COIL+), K4.1 (COIL+), K5.1 (COIL+), K6.1 (COIL+), K7.1 (COIL+), K8.1 (COIL+); also elsewhere on the board
+Relay_External: K2.3 (COM_1), K2.6 (COM_2), K3.3 (COM_1), K3.6 (COM_2), K4.3 (COM_1), K4.6 (COM_2), K5.3 (COM_1), K5.6 (COM_2), K6.3 (COM_1), K6.6 (COM_2), K7.3 (COM_1), K7.6 (COM_2), K8.3 (COM_1), K8.6 (COM_2); also elsewhere on the board
/Microcontroller Page 1 (PA_PB)/D30_RLY_8: R131.2, R132.1; also elsewhere on the board
/Microcontroller Page 1 (PA_PB)/D31_RLY_7: R128.2, R129.1; also elsewhere on the board
/Microcontroller Page 1 (PA_PB)/D32_RLY_6: R125.2, R126.1; also elsewhere on the board
/Microcontroller Page 1 (PA_PB)/D33_RLY_5: R122.2, R123.1; also elsewhere on the board
/Microcontroller Page 1 (PA_PB)/D34_RLY_4: R119.2, R120.1; also elsewhere on the board
/Microcontroller Page 1 (PA_PB)/D35_RLY_3: R116.2, R117.1; also elsewhere on the board
/Microcontroller Page 1 (PA_PB)/D36_RLY_2: R113.2, R114.1; also elsewhere on the board
/Relay_2/Relay_NC: K2.2 (NC_1), K2.7 (NC_2); also elsewhere on the board
/Relay_2/Relay_NO: K2.4 (NO_1), K2.5 (NO_2); also elsewhere on the board
/Relay_3/Relay_NC: K3.2 (NC_1), K3.7 (NC_2); also elsewhere on the board
/Relay_3/Relay_NO: K3.4 (NO_1), K3.5 (NO_2); also elsewhere on the board
/Relay_4/Relay_NC: K4.2 (NC_1), K4.7 (NC_2); also elsewhere on the board
/Relay_4/Relay_NO: K4.4 (NO_1), K4.5 (NO_2); also elsewhere on the board
/Relay_5/Relay_NC: K5.2 (NC_1), K5.7 (NC_2); also elsewhere on the board
/Relay_5/Relay_NO: K5.4 (NO_1), K5.5 (NO_2); also elsewhere on the board
/Relay_6/Relay_NC: K6.2 (NC_1), K6.7 (NC_2); also elsewhere on the board
/Relay_6/Relay_NO: K6.4 (NO_1), K6.5 (NO_2); also elsewhere on the board
/Relay_7/Relay_NC: K7.2 (NC_1), K7.7 (NC_2); also elsewhere on the board
/Relay_7/Relay_NO: K7.4 (NO_1), K7.5 (NO_2); also elsewhere on the board
/Relay_8/Relay_NC: K8.2 (NC_1), K8.7 (NC_2); also elsewhere on the board
/Relay_8/Relay_NO: K8.4 (NO_1), K8.5 (NO_2); also elsewhere on the board
GND: Q3.2 (S), Q4.2 (S), Q5.2 (S), Q6.2 (S), Q7.2 (S), Q8.2 (S), Q9.2 (S), R114.2, R117.2, R120.2, R123.2, R126.2, R129.2, R132.2; also elsewhere on the board
unnamed: D18.2 (A), K2.8 (COIL-), Q3.3 (D), R115.2
unnamed: D19.1 (K), R115.1
unnamed: D20.2 (A), K3.8 (COIL-), Q4.3 (D), R118.2
unnamed: D21.1 (K), R118.1
unnamed: D22.2 (A), K4.8 (COIL-), Q5.3 (D), R121.2
unnamed: D23.1 (K), R121.1
unnamed: D24.2 (A), K5.8 (COIL-), Q6.3 (D), R124.2
unnamed: D25.1 (K), R124.1
unnamed: D26.2 (A), K6.8 (COIL-), Q7.3 (D), R127.2
unnamed: D27.1 (K), R127.1
unnamed: D28.2 (A), K7.8 (COIL-), Q8.3 (D), R130.2
unnamed: D29.1 (K), R130.1
unnamed: D30.2 (A), K8.8 (COIL-), Q9.3 (D), R133.2
unnamed: D31.1 (K), R133.1
unnamed: Q3.1 (G), R113.1
unnamed: Q4.1 (G), R116.1
unnamed: Q5.1 (G), R119.1
unnamed: Q6.1 (G), R122.1
unnamed: Q7.1 (G), R125.1
unnamed: Q8.1 (G), R128.1
unnamed: Q9.1 (G), R131.1

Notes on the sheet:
TARTARUS
AD ASTRA FROM THE ABYSS
